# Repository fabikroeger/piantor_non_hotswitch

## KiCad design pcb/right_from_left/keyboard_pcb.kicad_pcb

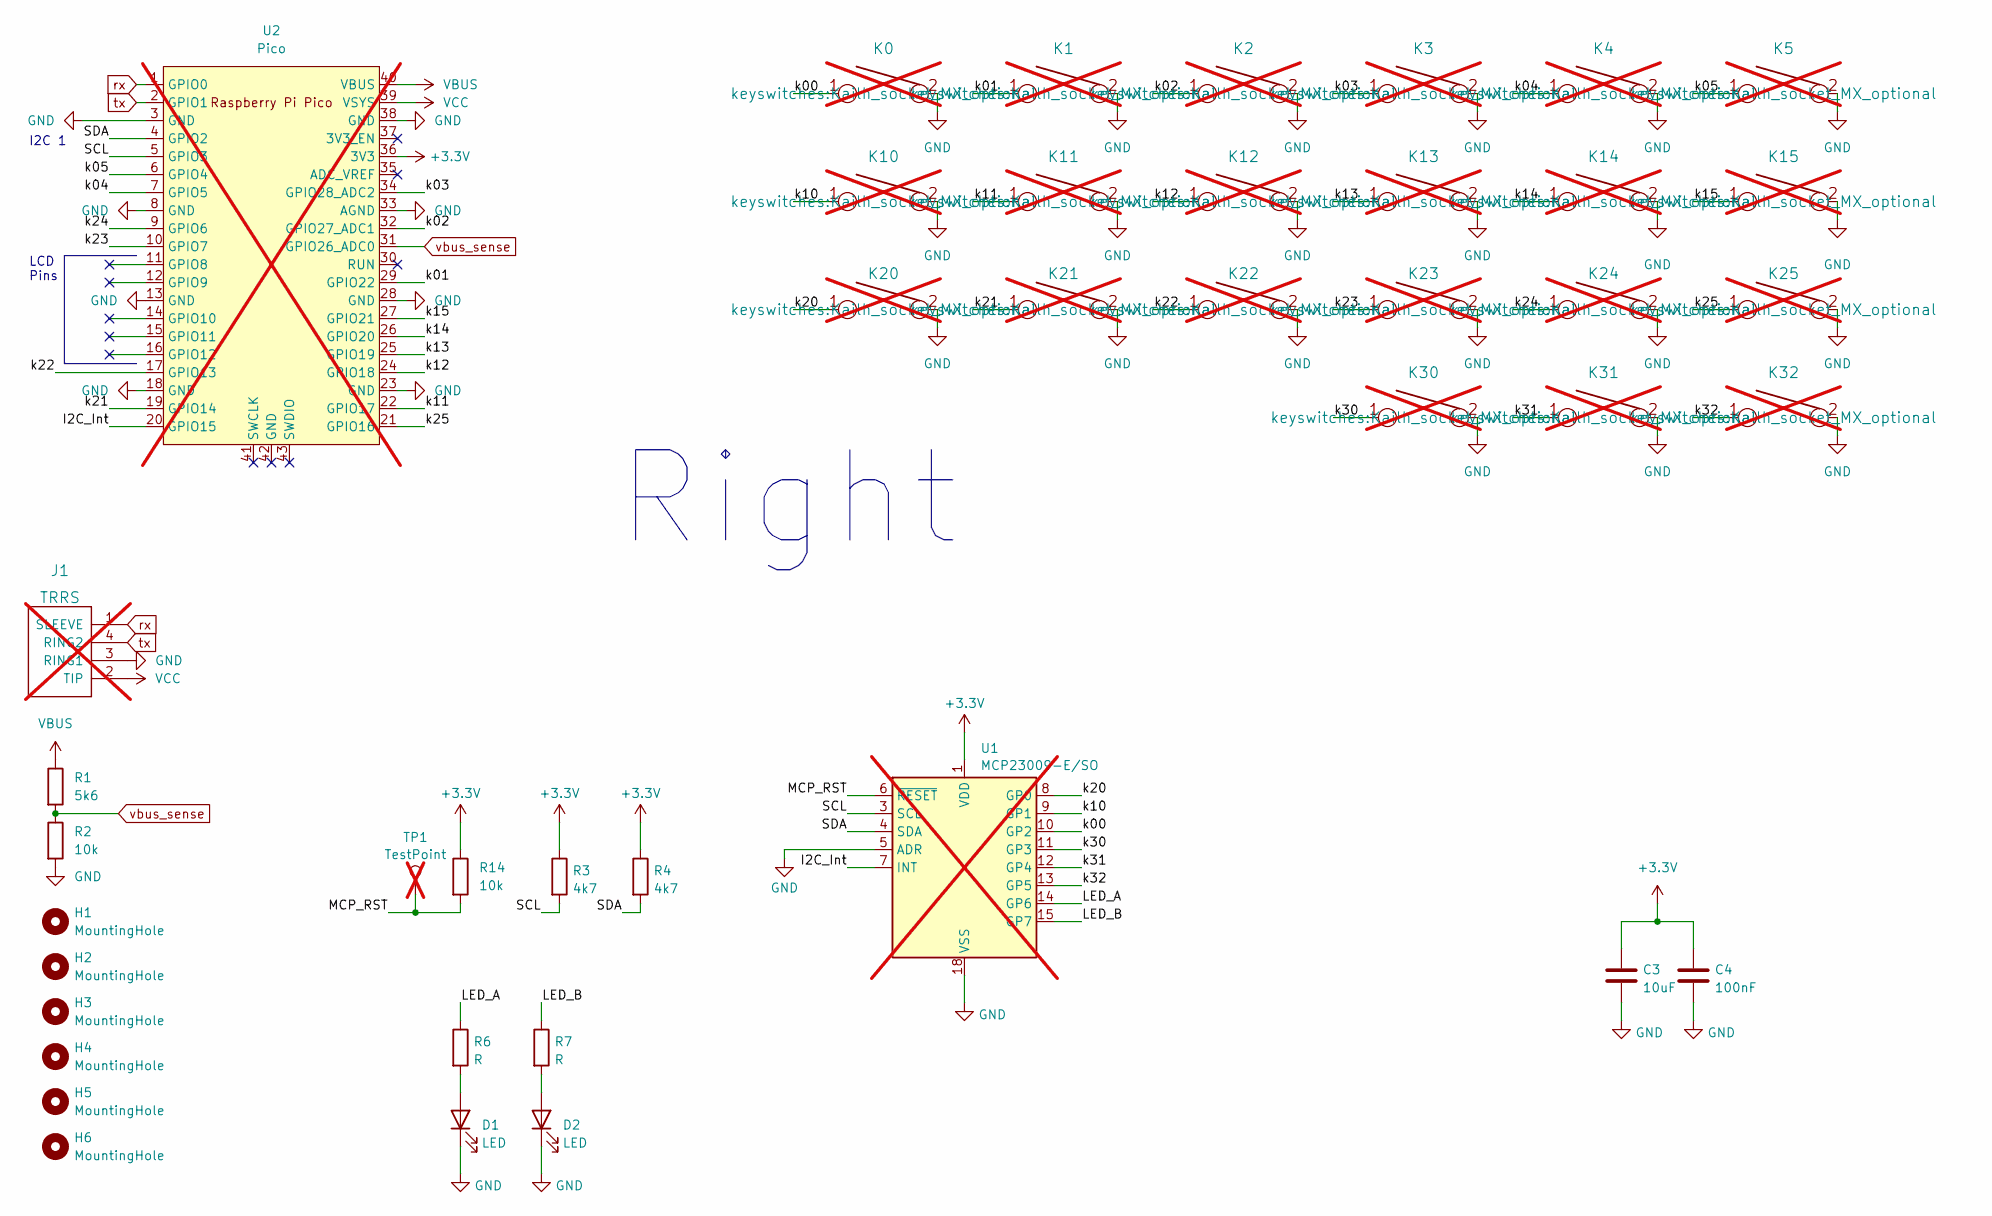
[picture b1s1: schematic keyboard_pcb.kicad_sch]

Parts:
C3: 10uF; C_0603_1608Metric_Pad1.08x0.95mm_HandSolder
C4: 100nF; C_0603_1608Metric_Pad1.08x0.95mm_HandSolder
D1, D2: LED; LED_0603_1608Metric
H1, H2, H3, H4, H5, H6: MountingHole; MountingHole_3.7mm_Pad_TopBottom
J1: TRRS; TRRS-PJ-320A_fab; not fitted
K0, K1, K2, K3, K4, K5, K10, K11, K12, K13, K14, K15, K20, K21, K22, K23, K24, K25, K30, K31, K32: KEYSW; Kailh_socket_MX_optional_platemount_3d_pretty_by_datasheet; not fitted
R1: 5k6; R_0603_1608Metric
R2, R14: 10k; R_0603_1608Metric
R3, R4: 4k7; R_0603_1608Metric
R6, R7: R; R_0603_1608Metric
TP1: TestPoint; TestPoint_Pad_D3.0mm; not fitted
U1: MCP23009-E/SO; SOIC-18W_7.5x11.6mm_P1.27mm; not fitted
U2: Pico; RPi_Pico_SMD_TH; not fitted

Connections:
+3.3V: C3.1, C4.1, R3.1, R4.1, R14.1, U1.1 (VDD), U2.36 (3V3)
/I2C_Int: U1.7 (INT), U2.20 (GPIO15)
/LED_A: R6.1, U1.14 (GP6)
/LED_B: R7.1, U1.15 (GP7)
/MCP_RST: R14.2, TP1.1, U1.6 (~RESET)
/SCL: R3.2, U1.3 (SCL), U2.5 (GPIO3)
/SDA: R4.2, U1.4 (SDA), U2.4 (GPIO2)
/k00: K0.1, U1.10 (GP2)
/k01: K1.1, U2.29 (GPIO22)
/k02: K2.1, U2.32 (GPIO27_ADC1)
/k03: K3.1, U2.34 (GPIO28_ADC2)
/k04: K4.1, U2.7 (GPIO5)
/k05: K5.1, U2.6 (GPIO4)
/k10: K10.1, U1.9 (GP1)
/k11: K11.1, U2.22 (GPIO17)
/k12: K12.1, U2.24 (GPIO18)
/k13: K13.1, U2.25 (GPIO19)
/k14: K14.1, U2.26 (GPIO20)
/k15: K15.1, U2.27 (GPIO21)
/k20: K20.1, U1.8 (GP0)
/k21: K21.1, U2.19 (GPIO14)
/k22: K22.1, U2.17 (GPIO13)
/k23: K23.1, U2.10 (GPIO7)
/k24: K24.1, U2.9 (GPIO6)
/k25: K25.1, U2.21 (GPIO16)
/k30: K30.1, U1.11 (GP3)
/k31: K31.1, U1.12 (GP4)
/k32: K32.1, U1.13 (GP5)
GND: C3.2, C4.2, D1.1 (K), D2.1 (K), J1.3 (RING1), K0.2, K1.2, K2.2, K3.2, K4.2, K5.2, K10.2, K11.2, K12.2, K13.2, K14.2, K15.2, K20.2, K21.2, K22.2, K23.2, K24.2, K25.2, K30.2, K31.2, K32.2, R2.2, U1.5 (ADR), U1.18 (VSS), U2.3 (GND), U2.8 (GND), U2.13 (GND), U2.18 (GND), U2.23 (GND), U2.28 (GND), U2.33 (AGND), U2.38 (GND)
unnamed: D1.2 (A), R6.2
unnamed: D2.2 (A), R7.2
VBUS: R1.1, U2.40 (VBUS)
VCC: J1.2 (TIP), U2.39 (VSYS)
rx: J1.1 (SLEEVE), U2.1 (GPIO0)
tx: J1.4 (RING2), U2.2 (GPIO1)
vbus_sense: R1.2, R2.1, U2.31 (GPIO26_ADC0)

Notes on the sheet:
LCD Pins
Right
I2C 1

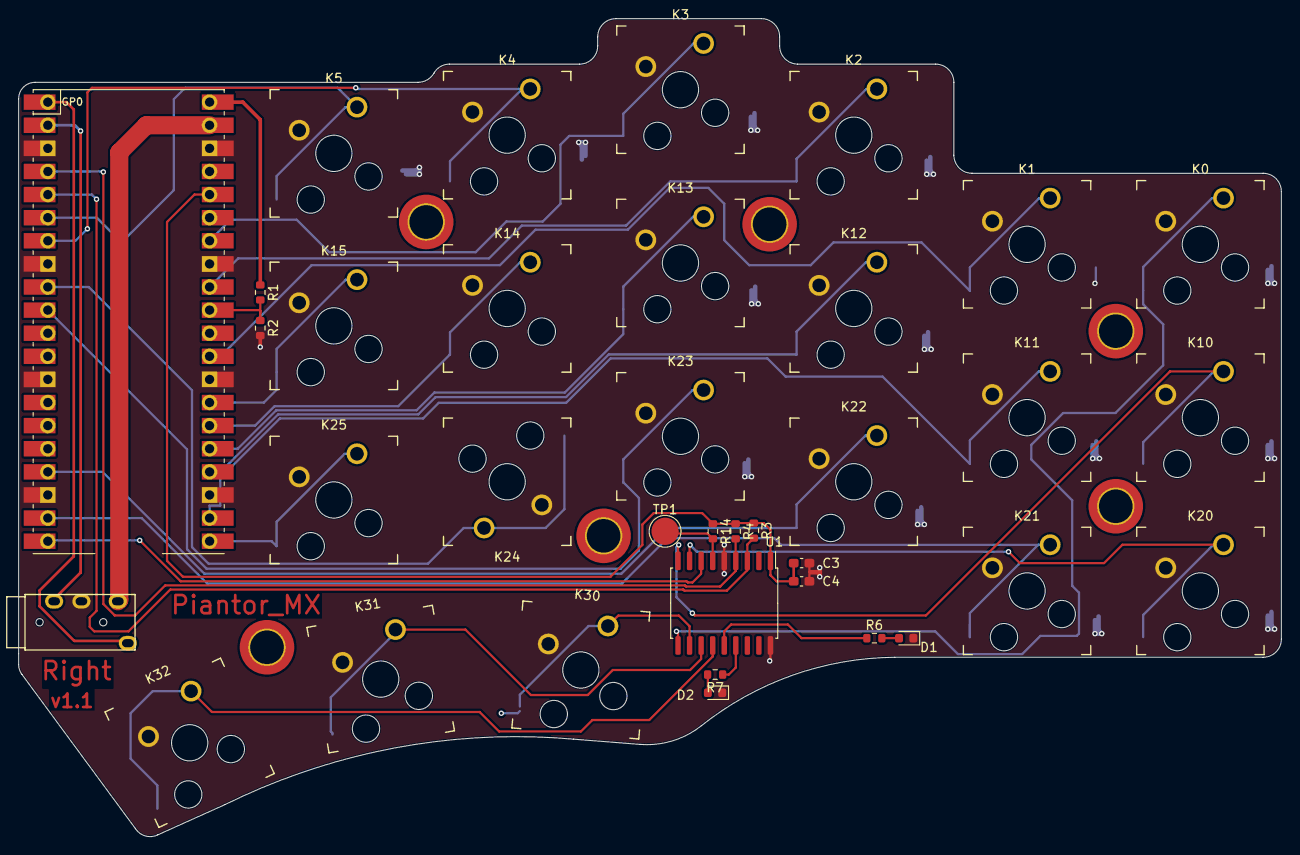
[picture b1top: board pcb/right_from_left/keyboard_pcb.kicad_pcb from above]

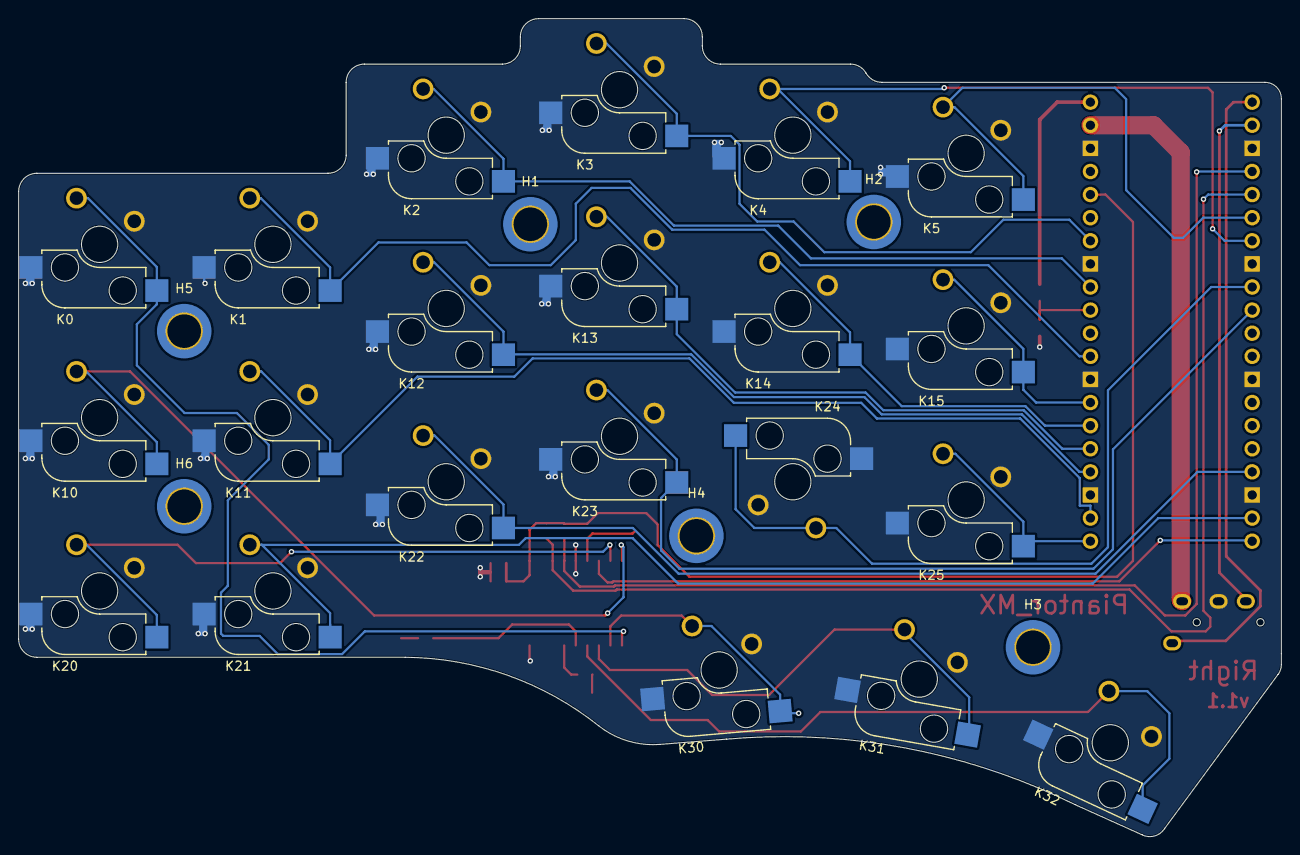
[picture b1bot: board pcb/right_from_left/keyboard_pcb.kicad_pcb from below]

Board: 2 copper layers, 138.8 x 89.9 mm, 42 parts (6 on the bottom side), 36 nets.

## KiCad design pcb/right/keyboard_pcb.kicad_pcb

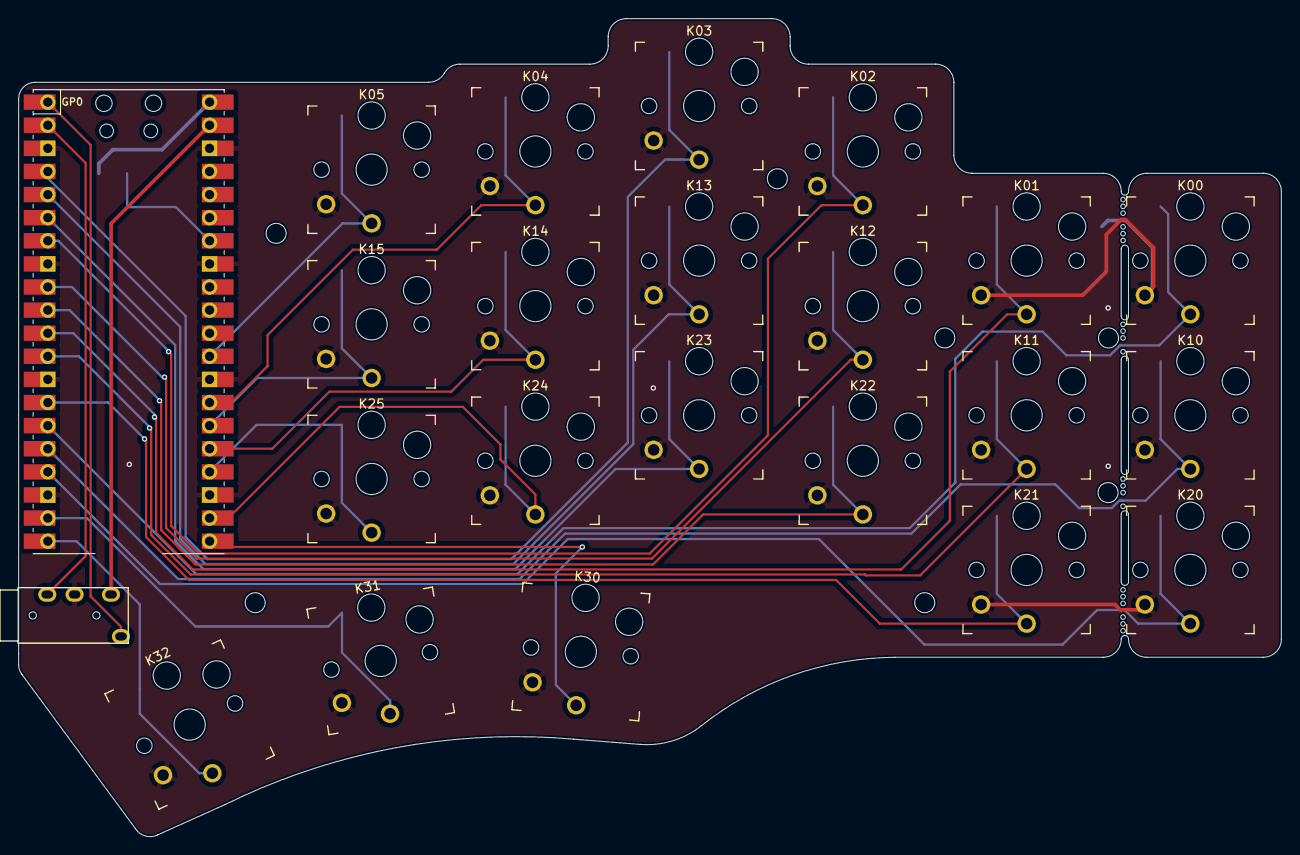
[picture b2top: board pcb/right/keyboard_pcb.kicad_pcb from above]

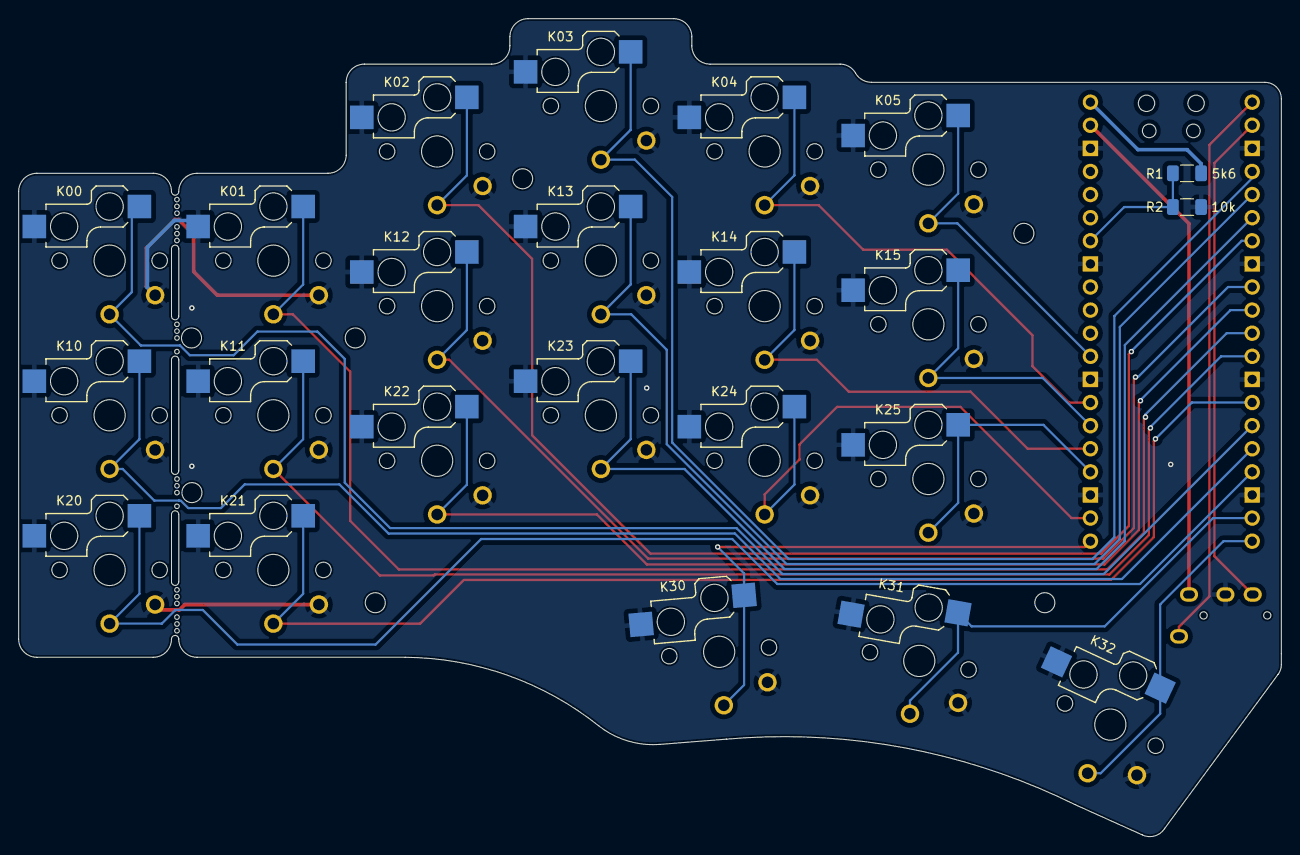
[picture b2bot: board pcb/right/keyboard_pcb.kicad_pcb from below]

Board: 2 copper layers, 138.8 x 89.9 mm, 36 parts (13 on the bottom side), 27 nets.

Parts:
H1, H1#2, H2, H3, H4, H4#2, H4#3: MountingHole; MountingHole_2.2mm_M2-8mm
J1: TRRS; TRRS-PJ-320A
K00, K01, K02, K03, K04, K05, K10, K11, K12, K13, K14, K15, K20, K21, K22, K23, K24, K25, K30, K31, K32: KEYSW; Kailh_socket_PG1350_optional
MB1, MB2: MountingHole; mousebites_2
MB3, MB4: MountingHole; mousebites_3
R1: 5k6; R_1206_3216Metric_Pad1.30x1.75mm_HandSolder
R2: 10k; R_1206_3216Metric_Pad1.30x1.75mm_HandSolder
U2: Pico; RPi_Pico_SMD_TH

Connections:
/k00: K00.1, U2.15 (GPIO11)
/k01: K01.1, U2.11 (GPIO8)
/k02: K02.1, U2.7 (GPIO5)
/k03: K03.1, U2.4 (GPIO2)
/k04: K04.1, U2.27 (GPIO21)
/k05: K05.1, U2.29 (GPIO22)
/k10: K10.1, U2.16 (GPIO12)
/k11: K11.1, U2.12 (GPIO9)
/k12: K12.1, U2.9 (GPIO6)
/k13: K13.1, U2.5 (GPIO3)
/k14: K14.1, U2.25 (GPIO19)
/k15: K15.1, U2.26 (GPIO20)
/k20: K20.1, U2.17 (GPIO13)
/k21: K21.1, U2.14 (GPIO10)
/k22: K22.1, U2.10 (GPIO7)
/k23: K23.1, U2.6 (GPIO4)
/k24: K24.1, U2.22 (GPIO17)
/k25: K25.1, U2.24 (GPIO18)
/k30: K30.1, U2.21 (GPIO16)
/k31: K31.1, U2.19 (GPIO14)
/k32: K32.1, U2.20 (GPIO15)
GND: J1.3 (RING1), K00.2, K01.2, K02.2, K03.2, K04.2, K05.2, K10.2, K11.2, K12.2, K13.2, K14.2, K15.2, K20.2, K21.2, K22.2, K23.2, K24.2, K25.2, K30.2, K31.2, K32.2, R2.2, U2.3 (GND), U2.8 (GND), U2.13 (GND), U2.18 (GND), U2.23 (GND), U2.28 (GND), U2.33 (AGND), U2.38 (GND)
VBUS: R1.1, U2.40 (VBUS)
VCC: J1.2 (TIP), U2.39 (VSYS)
rx: J1.4 (RING2), U2.2 (GPIO1)
tx: J1.1 (SLEEVE), U2.1 (GPIO0)
vbus_sense: R1.2, R2.1, U2.34 (GPIO28_ADC2)

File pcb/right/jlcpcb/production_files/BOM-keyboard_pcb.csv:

Comment,Designator,Footprint,LCSC
KEYSW,K25,Kailh_socket_PG1350_optional,
KEYSW,K24,Kailh_socket_PG1350_optional,
KEYSW,K21,Kailh_socket_PG1350_optional,
KEYSW,K02,Kailh_socket_PG1350_optional,
KEYSW,K10,Kailh_socket_PG1350_optional,
Pico,U2,RPi_Pico_SMD_TH,
KEYSW,K04,Kailh_socket_PG1350_optional,
KEYSW,K12,Kailh_socket_PG1350_optional,
KEYSW,K30,Kailh_socket_PG1350_optional,
KEYSW,K01,Kailh_socket_PG1350_optional,
KEYSW,K14,Kailh_socket_PG1350_optional,
KEYSW,K23,Kailh_socket_PG1350_optional,
KEYSW,K03,Kailh_socket_PG1350_optional,
KEYSW,K22,Kailh_socket_PG1350_optional,
KEYSW,K15,Kailh_socket_PG1350_optional,
KEYSW,K32,Kailh_socket_PG1350_optional,
KEYSW,K11,Kailh_socket_PG1350_optional,
KEYSW,K05,Kailh_socket_PG1350_optional,
KEYSW,K20,Kailh_socket_PG1350_optional,
KEYSW,K13,Kailh_socket_PG1350_optional,
KEYSW,K00,Kailh_socket_PG1350_optional,
KEYSW,K31,Kailh_socket_PG1350_optional,
10k,R2,R_1206_3216Metric_Pad1.30x1.75mm_HandSolder,
MountingHole,H4,MountingHole_2.2mm_M2-8mm,
MountingHole,H2,MountingHole_2.2mm_M2-8mm,
MountingHole,MB1,mousebites_2,
5k6,R1,R_1206_3216Metric_Pad1.30x1.75mm_HandSolder,
MountingHole,MB3,mousebites_3,
MountingHole,MB2,mousebites_2,
MountingHole,H1,MountingHole_2.2mm_M2-8mm,
MountingHole,H3,MountingHole_2.2mm_M2-8mm,
MountingHole,MB4,mousebites_3,

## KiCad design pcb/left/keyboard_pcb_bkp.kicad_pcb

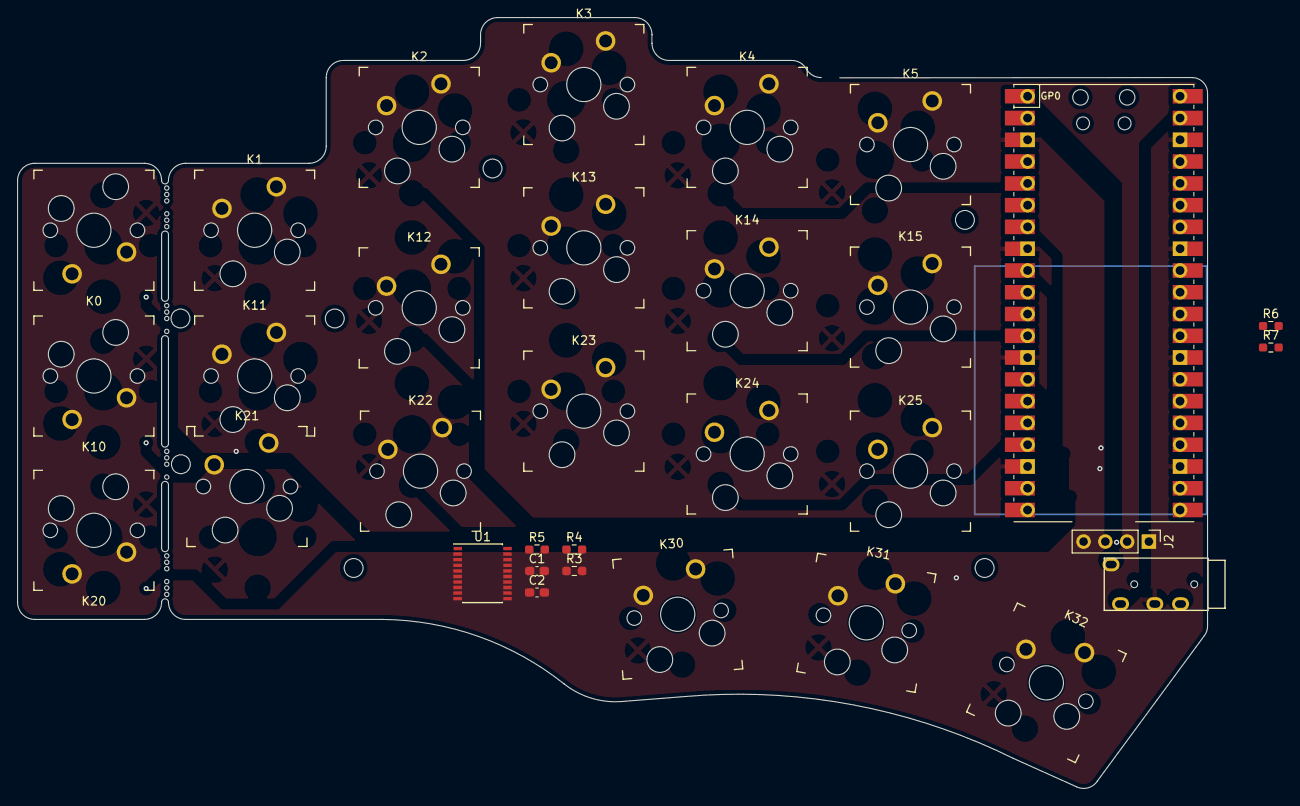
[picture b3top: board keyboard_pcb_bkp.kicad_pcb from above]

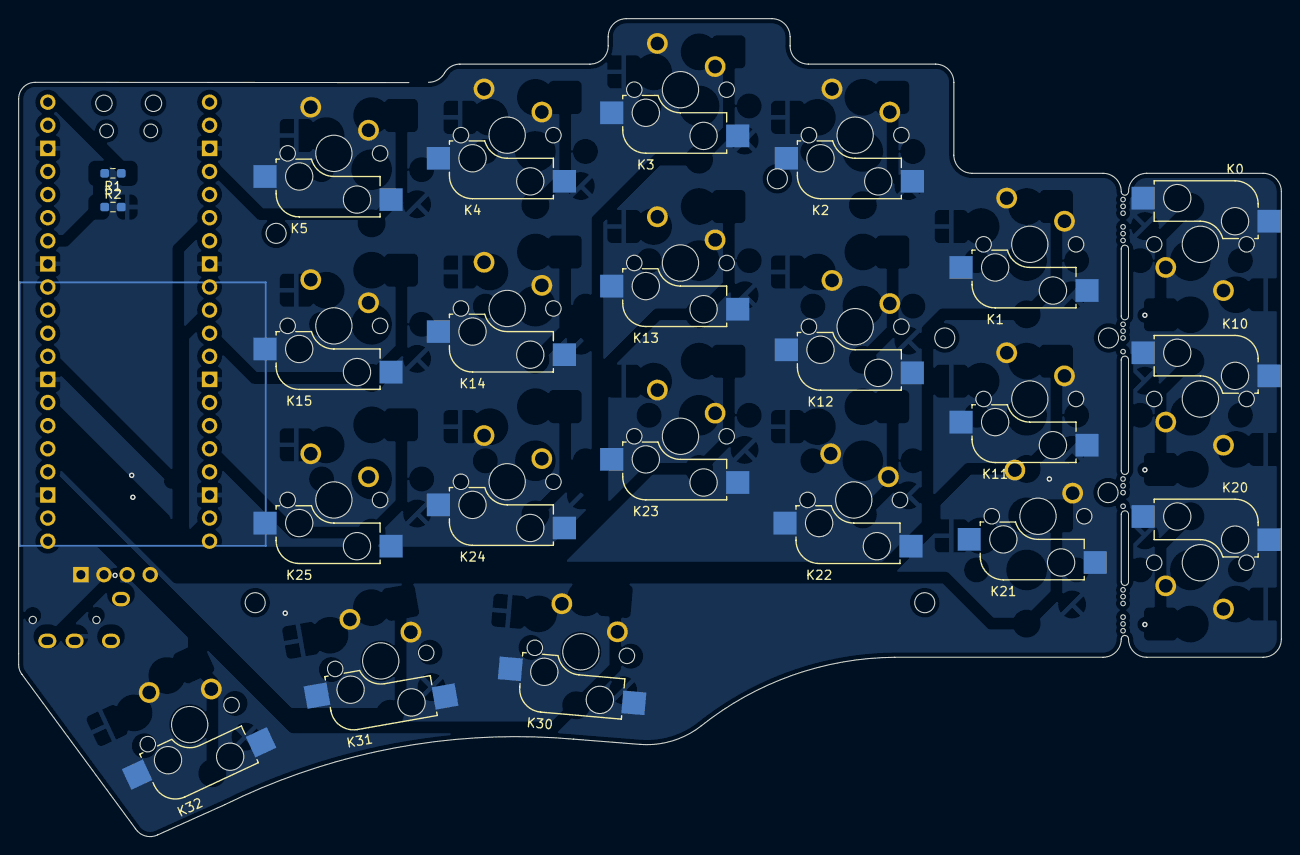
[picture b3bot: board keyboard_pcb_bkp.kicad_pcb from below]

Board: 2 copper layers, 138.8 x 89.9 mm, 45 parts (2 on the bottom side), 32 nets, no tracks yet.

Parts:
C1, C2: C; C_0603_1608Metric_Pad1.08x0.95mm_HandSolder
H1, H1#2, H2, H3, H4, H4#2, H4#3: MountingHole; MountingHole_2.2mm_M2-8mm
J1: TRRS; TRRS-PJ-320A
J2: Conn_01x04_Male; PinHeader_1x04_P2.54mm_Vertical
K0, K1, K2, K3, K4, K5, K10, K11, K12, K13, K14, K15, K20, K21, K22, K23, K24, K25, K30, K31, K32: KEYSW; Kailh_socket_MX_optional
MB1, MB2: MountingHole; mousebites_2
MB3, MB4: MountingHole; mousebites_3
R1: 5k6; R_0603_1608Metric_Pad0.98x0.95mm_HandSolder
R2, R5: 10k; R_0603_1608Metric_Pad0.98x0.95mm_HandSolder
R3, R4, R6, R7: R; R_0603_1608Metric_Pad0.98x0.95mm_HandSolder
U1: PCF8574; SSOP-20_4.4x6.5mm_P0.65mm
U2: Pico; RPi_Pico_SMD_TH

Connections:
/I2C_Int: R5.2, U1.13 (~INT), U2.27 (GPIO21)
/LED_A: R6.1, U1.11 (P6)
/LED_B: R7.1, U1.12 (P7)
/SCL: J2.2, R3.2, U1.14 (SCL), U2.32 (GPIO27_ADC1)
/SDA: J2.1, R4.2, U1.15 (SDA), U2.31 (GPIO26_ADC0)
/k00: K0.1, U1.4 (P0)
/k01: K1.1, U2.29 (GPIO22)
/k02: K2.1, U2.7 (GPIO5)
/k03: K3.1, U2.20 (GPIO15)
/k04: K4.1, U2.5 (GPIO3)
/k05: K5.1, U2.4 (GPIO2)
/k10: K10.1, U1.5 (P1)
/k11: K11.1, U2.26 (GPIO20)
/k12: K12.1, U2.24 (GPIO18)
/k13: K13.1, U2.19 (GPIO14)
/k14: K14.1, U2.22 (GPIO17)
/k15: K15.1, U2.21 (GPIO16)
/k20: K20.1, U1.6 (P2)
/k21: K21.1, U2.25 (GPIO19)
/k22: K22.1, U2.9 (GPIO6)
/k23: K23.1, U2.10 (GPIO7)
/k24: K24.1, U2.17 (GPIO13)
/k25: K25.1, U2.6 (GPIO4)
/k30: K30.1, U1.9 (P4)
/k31: K31.1, U1.7 (P3)
/k32: K32.1, U1.10 (P5)
GND: C1.2, C2.2, J1.3 (RING1), J2.4, K0.2, K1.2, K2.2, K3.2, K4.2, K5.2, K10.2, K11.2, K12.2, K13.2, K14.2, K15.2, K20.2, K21.2, K22.2, K23.2, K24.2, K25.2, K30.2, K31.2, K32.2, R2.2, U1.1 (A0), U1.2 (A1), U1.3 (A2), U1.8 (VSS), U2.3 (GND), U2.8 (GND), U2.13 (GND), U2.18 (GND), U2.23 (GND), U2.28 (GND), U2.33 (AGND), U2.38 (GND)
VBUS: R1.1, U2.40 (VBUS)
VCC: C1.1, C2.1, J1.2 (TIP), J2.3, R3.1, R4.1, R5.1, U1.16 (VDD), U2.39 (VSYS)
rx: J1.1 (SLEEVE), U2.2 (GPIO1)
tx: J1.4 (RING2), U2.1 (GPIO0)
vbus_sense: R1.2, R2.1, U2.34 (GPIO28_ADC2)

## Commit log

2023-01-27 Added GPIO portexpander, Pin remapping, added LEDs WIP!
2023-02-16 Now there are MX switches on the pcb, 3d check via printing the pcb and populating the switches with caps
2023-02-16 added the TRRS jack with a fablayer for the mechanical design
2023-02-16 save - to be squashed
2023-02-22 first layout left
2023-02-22 added pcb/right_from_left with Kicad-nightly aka 7.0ish dataformat
2023-02-24 right_from_left is ready for review
2023-03-02 Added changes on the left board
2023-03-04 Mechanical parts are "mirrored", ToDo: Pin header LCD i2c pinheader needs alignment
2023-03-05 left keyboards routed
2023-03-05 Minor changes
2023-03-08 Schematics are now Kicad 7 compatible
2023-03-08 Left keyboard: Jumper to switch RX/TX direction removed in schematic and pcb.
2023-07-19 finetuning regarding BOM and part placement
2023-11-19 v1.0
2024-01-06 Revision 1.1 WIP#
2024-01-08 Left side routing wip
2024-01-08 Revision 1.1 WIP; left pcb -RFR-
2024-01-08 Rev 1.1 WIP
2024-03-18 Revision 1.1 -RFR- new standoff holes added and left/right pcb positions synced
2024-04-21 Revision 1.1 -RFR- right pcb layout fix
2024-04-25 Revision 1.1 -RFR- right pcb layout fix added Standoff PN
